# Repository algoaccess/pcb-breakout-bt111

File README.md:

# pcb-breakout-bt111
Pin breakout of the Bluegiga BT111 board to through-hole pin headers for prototyping. 

##PCB Design software and addons used

1. Eagle 7.5.0: I use Standard but Light should still be able to open/modify the files.
2. BT111 library by [jshrowberg](https://github.com/jrowberg/sf-oshw/tree/master/bluegiga/eagle) (in repo as sf-bluegiga.lbr)

##Images
None at this time

##Schematic drawings
Images are exported from Eagle at 600dpi.

##Parts required

The BT111 module can be bought from one of the online stores like [Mouser](http://www.mouser.sg/ProductDetail/Bluegiga-Technologies/BT111-A-HCI/?qs=%2fha2pyFaduivsoc9o%252b2ay07XF51Ha8cewDylb7jSEvcMIawLVwDmnw%3d%3d)

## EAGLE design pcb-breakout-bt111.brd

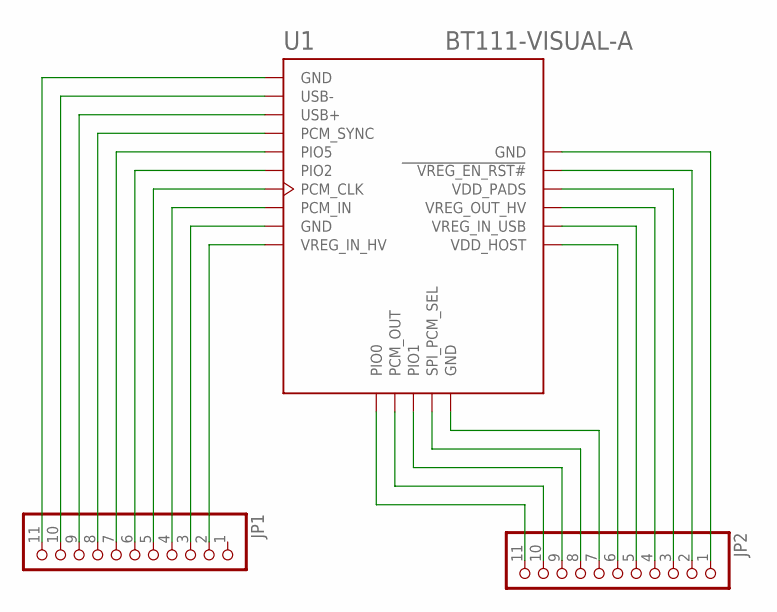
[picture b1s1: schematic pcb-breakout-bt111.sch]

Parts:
JP1, JP2: PINHD-1X11; 1X11
U1: BT111-VISUAL-A; BT111-A

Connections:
unnamed: JP1.11, U1.GND
unnamed: JP1.10, U1.USB-
unnamed: JP1.9, U1.USB+
unnamed: JP2.1, U1.GND@4 (GND)
unnamed: JP2.2, U1.VREG_EN_RST#
unnamed: JP2.3, U1.VDD_PADS
unnamed: JP2.4, U1.VREG_OUT_HV
unnamed: JP2.5, U1.VREG_IN_USB
unnamed: JP2.6, U1.VDD_HOST
unnamed: JP1.8, U1.PCM_SYNC
unnamed: JP1.7, U1.PIO5
unnamed: JP1.6, U1.PIO2
unnamed: JP1.5, U1.PCM_CLK
unnamed: JP1.4, U1.PCM_IN
unnamed: JP1.3, U1.GND@2 (GND)
unnamed: JP1.2, U1.VREG_IN_HV
unnamed: JP2.7, U1.GND@3 (GND)
unnamed: JP2.8, U1.SPI_PCM_SEL
unnamed: JP2.9, U1.PIO1
unnamed: JP2.10, U1.PCM_OUT
unnamed: JP2.11, U1.PIO0

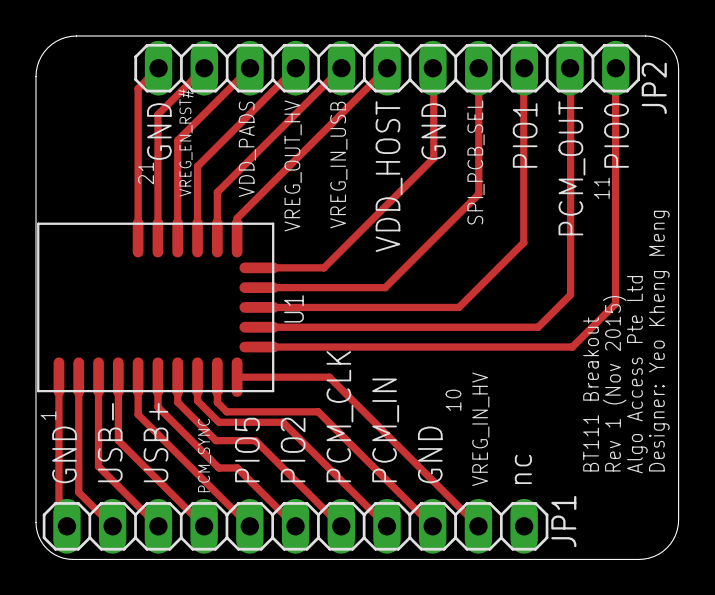
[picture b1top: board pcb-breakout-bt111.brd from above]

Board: 2 copper layers, 35.7 x 29.1 mm, 3 parts (0 on the bottom side), 21 nets.

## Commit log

2015-11-18 pin numbering in silkscreen
2015-11-18 miter corners
2015-11-18 images and gerbels
